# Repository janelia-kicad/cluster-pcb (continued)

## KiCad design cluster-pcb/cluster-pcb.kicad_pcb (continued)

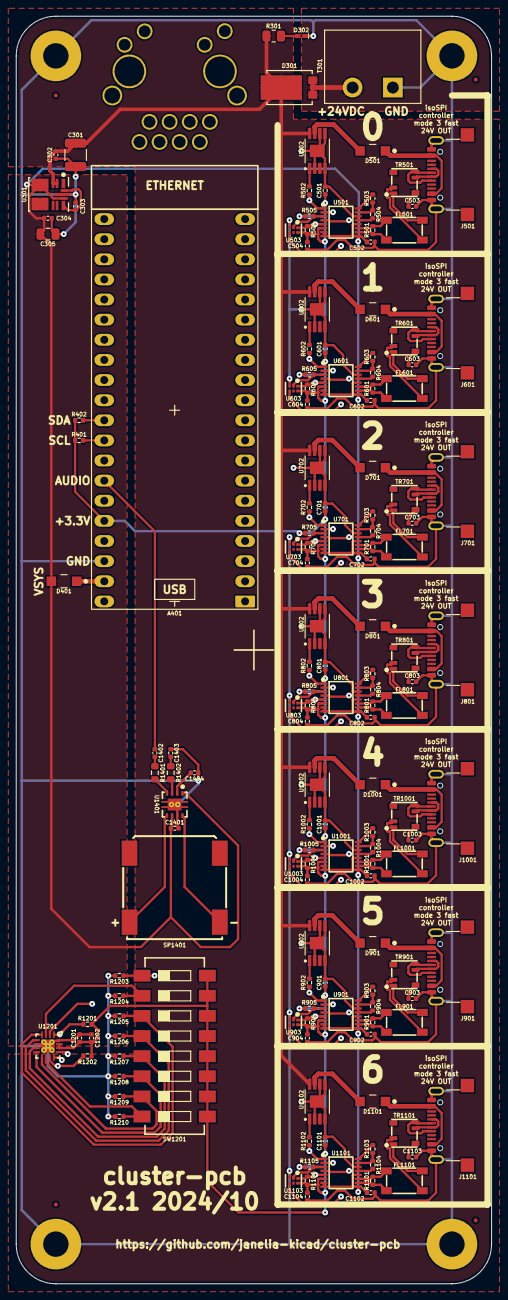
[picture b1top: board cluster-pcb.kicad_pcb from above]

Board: 4 copper layers, 60.0 x 160.0 mm, 163 parts (0 on the bottom side), 130 nets.

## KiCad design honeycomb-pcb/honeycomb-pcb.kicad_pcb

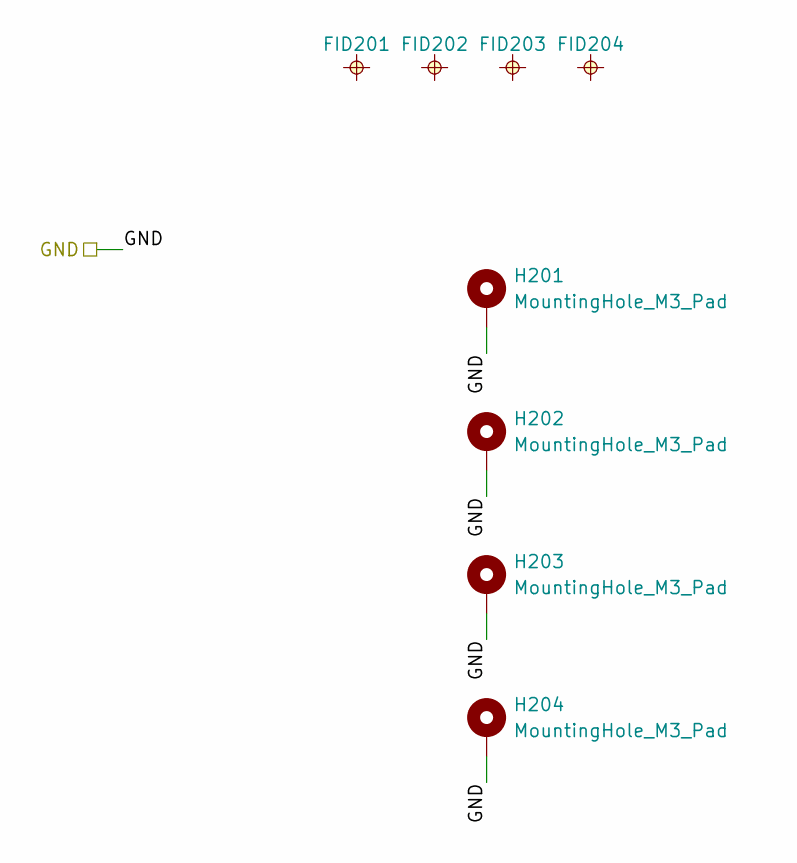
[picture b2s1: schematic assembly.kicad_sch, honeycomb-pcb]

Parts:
FID201, FID202, FID203, FID204: FIDUCIAL_0.5mm_MASK1mm; FIDUCIAL_0.5mm_Mask1mm
H201, H202, H203, H204: MountingHole_M3_Pad; MountingHole_3.2mm_M3_Pad

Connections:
/GND: H201.1, H202.1, H203.1, H204.1; also elsewhere on the board

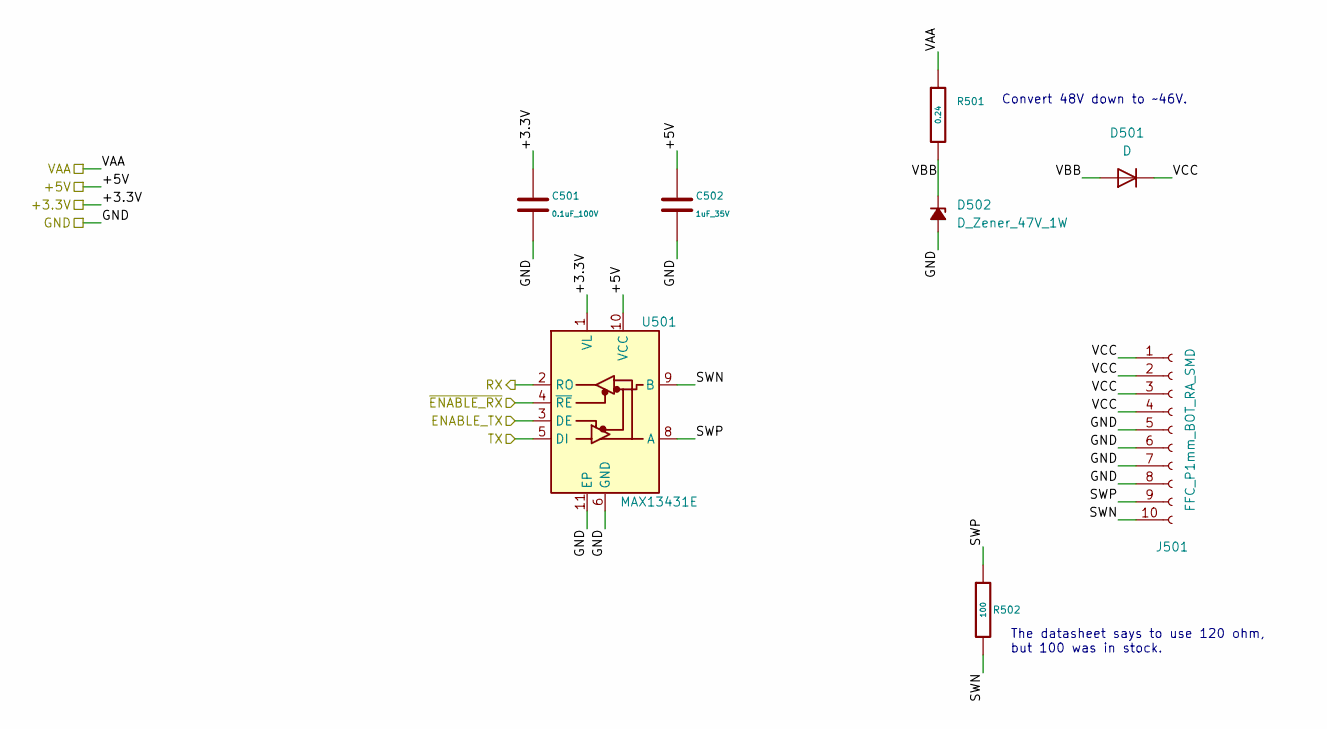
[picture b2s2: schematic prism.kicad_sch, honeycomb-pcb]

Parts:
C501: 0.1uF_100V; C_0402_1005Metric; Manufacturer Part Number GRM155R62A104KE14D; LCSC C162178
C502: 1uF_35V; C_0402_1005Metric; Manufacturer Part Number CL05A105KL5NRNC; LCSC C307413
D501: D; D_SMB; Manufacturer Part Number ES2G; LCSC C4944961
D502: D_Zener_47V_1W; D_SMA; Manufacturer Part Number 1SMAF4756A; LCSC C475448
J501: FFC_P1mm_BOT_RA_SMD; CONN_C2914097; Manufacturer Part Number 1.0K-FX-10PWBG; LCSC C2914097
R501: 0.24; R_2512_6332Metric; Manufacturer Part Number FRL2512JR240TS; LCSC C2960776
R502: 100; R_0402_1005Metric; Manufacturer Part Number 0402WGF1000TCE; LCSC C25076
U501: MAX13431E; 21-0137I_T1033-1_MXM; Manufacturer Part Number MAX13431EETB+T; LCSC C2672811

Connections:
/+3.3V: C501.1, U501.1 (VL); also elsewhere on the board
/+5V: C502.1, U501.10 (VCC); also elsewhere on the board
/ENABLE_TX_0: U501.3 (DE); also elsewhere on the board
/GND: C501.2, C502.2, D502.2 (A), J501.5, J501.6, J501.7, J501.8, U501.6 (GND), U501.11 (EP); also elsewhere on the board
/RX: U501.2 (RO); also elsewhere on the board
/TX: U501.5 (DI); also elsewhere on the board
/VCC: R501.1; also elsewhere on the board
/prism0/SWN: J501.10, R502.2, U501.9 (B)
/prism0/SWP: J501.9, R502.1, U501.8 (A)
/prism0/VBB: D501.2 (A), D502.1 (K), R501.2
/prism0/VCC: D501.1 (K), J501.1, J501.2, J501.3, J501.4
/~ENABLE_RX_0: U501.4 (~RE); also elsewhere on the board

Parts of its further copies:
C601, C701, C801, C901, C1001, C1101: 0.1uF_100V; C_0402_1005Metric; Manufacturer Part Number GRM155R62A104KE14D; LCSC C162178
C602, C702, C802, C902, C1002, C1102: 1uF_35V; C_0402_1005Metric; Manufacturer Part Number CL05A105KL5NRNC; LCSC C307413
D601, D701, D801, D901, D1001, D1101: D; D_SMB; Manufacturer Part Number ES2G; LCSC C4944961
D602, D702, D802, D902, D1002, D1102: D_Zener_47V_1W; D_SMA; Manufacturer Part Number 1SMAF4756A; LCSC C475448
J601, J701, J801, J901, J1001, J1101: FFC_P1mm_BOT_RA_SMD; CONN_C2914097; Manufacturer Part Number 1.0K-FX-10PWBG; LCSC C2914097
R601, R701, R801, R901, R1001, R1101: 0.24; R_2512_6332Metric; Manufacturer Part Number FRL2512JR240TS; LCSC C2960776
R602, R702, R802, R902, R1002, R1102: 100; R_0402_1005Metric; Manufacturer Part Number 0402WGF1000TCE; LCSC C25076
U601, U701, U801, U901, U1001, U1101: MAX13431E; 21-0137I_T1033-1_MXM; Manufacturer Part Number MAX13431EETB+T; LCSC C2672811

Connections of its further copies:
/+3.3V: C601.1, C701.1, C801.1, C901.1, C1001.1, C1101.1, U601.1 (VL), U701.1 (VL), U801.1 (VL), U901.1 (VL), U1001.1 (VL), U1101.1 (VL); also elsewhere on the board
/+5V: C602.1, C702.1, C802.1, C902.1, C1002.1, C1102.1, U601.10 (VCC), U701.10 (VCC), U801.10 (VCC), U901.10 (VCC), U1001.10 (VCC), U1101.10 (VCC); also elsewhere on the board
/ENABLE_TX_1: U601.3 (DE); also elsewhere on the board
/ENABLE_TX_2: U701.3 (DE); also elsewhere on the board
/ENABLE_TX_3: U801.3 (DE); also elsewhere on the board
/ENABLE_TX_4: U1001.3 (DE); also elsewhere on the board
/ENABLE_TX_5: U901.3 (DE); also elsewhere on the board
/ENABLE_TX_6: U1101.3 (DE); also elsewhere on the board
/GND: C601.2, C602.2, C701.2, C702.2, C801.2, C802.2, C901.2, C902.2, C1001.2, C1002.2, C1101.2, C1102.2, D602.2 (A), D702.2 (A), D802.2 (A), D902.2 (A), D1002.2 (A), D1102.2 (A), J601.5, J601.6, J601.7, J601.8, J701.5, J701.6, J701.7, J701.8, J801.5, J801.6, J801.7, J801.8, J901.5, J901.6, J901.7, J901.8, J1001.5, J1001.6, J1001.7, J1001.8, J1101.5, J1101.6, J1101.7, J1101.8, U601.6 (GND), U601.11 (EP), U701.6 (GND), U701.11 (EP), U801.6 (GND), U801.11 (EP), U901.6 (GND), U901.11 (EP), U1001.6 (GND), U1001.11 (EP), U1101.6 (GND), U1101.11 (EP); also elsewhere on the board
/RX: U601.2 (RO), U701.2 (RO), U801.2 (RO), U901.2 (RO), U1001.2 (RO), U1101.2 (RO); also elsewhere on the board
/TX: U601.5 (DI), U701.5 (DI), U801.5 (DI), U901.5 (DI), U1001.5 (DI), U1101.5 (DI); also elsewhere on the board
/VCC: R601.1, R701.1, R801.1, R901.1, R1001.1, R1101.1; also elsewhere on the board
/prism1/SWN: J601.10, R602.2, U601.9 (B)
/prism1/SWP: J601.9, R602.1, U601.8 (A)
/prism1/VBB: D601.2 (A), D602.1 (K), R601.2
/prism1/VCC: D601.1 (K), J601.1, J601.2, J601.3, J601.4
/prism2/SWN: J701.10, R702.2, U701.9 (B)
/prism2/SWP: J701.9, R702.1, U701.8 (A)
/prism2/VBB: D701.2 (A), D702.1 (K), R701.2
/prism2/VCC: D701.1 (K), J701.1, J701.2, J701.3, J701.4
/prism3/SWN: J801.10, R802.2, U801.9 (B)
/prism3/SWP: J801.9, R802.1, U801.8 (A)
/prism3/VBB: D801.2 (A), D802.1 (K), R801.2
/prism3/VCC: D801.1 (K), J801.1, J801.2, J801.3, J801.4
/prism4/SWN: J1001.10, R1002.2, U1001.9 (B)
/prism4/SWP: J1001.9, R1002.1, U1001.8 (A)
/prism4/VBB: D1001.2 (A), D1002.1 (K), R1001.2
/prism4/VCC: D1001.1 (K), J1001.1, J1001.2, J1001.3, J1001.4
/prism5/SWN: J901.10, R902.2, U901.9 (B)
/prism5/SWP: J901.9, R902.1, U901.8 (A)
/prism5/VBB: D901.2 (A), D902.1 (K), R901.2
/prism5/VCC: D901.1 (K), J901.1, J901.2, J901.3, J901.4
/prism6/SWN: J1101.10, R1102.2, U1101.9 (B)
/prism6/SWP: J1101.9, R1102.1, U1101.8 (A)
/prism6/VBB: D1101.2 (A), D1102.1 (K), R1101.2
/prism6/VCC: D1101.1 (K), J1101.1, J1101.2, J1101.3, J1101.4
/~ENABLE_RX_1: U601.4 (~RE); also elsewhere on the board
/~ENABLE_RX_2: U701.4 (~RE); also elsewhere on the board
/~ENABLE_RX_3: U801.4 (~RE); also elsewhere on the board
/~ENABLE_RX_4: U1001.4 (~RE); also elsewhere on the board
/~ENABLE_RX_5: U901.4 (~RE); also elsewhere on the board
/~ENABLE_RX_6: U1101.4 (~RE); also elsewhere on the board

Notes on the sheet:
The datasheet says to use 120 ohm, but 100 was in stock.
Convert 48V down to ~46V.

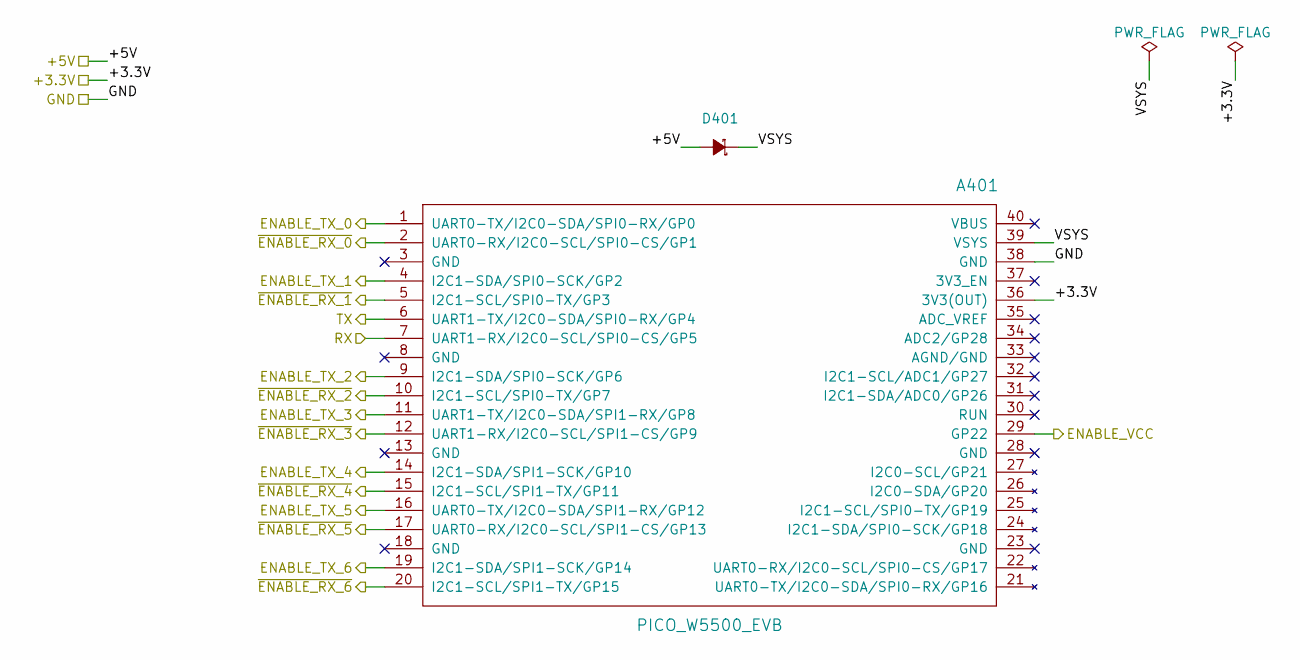
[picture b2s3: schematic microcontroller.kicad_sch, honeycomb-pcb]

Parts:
A401: PICO_W5500_EVB; Pico_Header_Holes
D401: D_SCHOTTKY_20V_1A; DIOM3616X98N; Manufacturer Part Number MBR120VLSFT1G; LCSC C223608

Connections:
/+3.3V: A401.36 (3V3(OUT)); also elsewhere on the board
/+5V: D401.2 (A); also elsewhere on the board
/ENABLE_TX_0: A401.1 (UART0-TX/I2C0-SDA/SPI0-RX/GP0); also elsewhere on the board
/ENABLE_TX_1: A401.4 (I2C1-SDA/SPI0-SCK/GP2); also elsewhere on the board
/ENABLE_TX_2: A401.9 (I2C1-SDA/SPI0-SCK/GP6); also elsewhere on the board
/ENABLE_TX_3: A401.11 (UART1-TX/I2C0-SDA/SPI1-RX/GP8); also elsewhere on the board
/ENABLE_TX_4: A401.14 (I2C1-SDA/SPI1-SCK/GP10); also elsewhere on the board
/ENABLE_TX_5: A401.16 (UART0-TX/I2C0-SDA/SPI1-RX/GP12); also elsewhere on the board
/ENABLE_TX_6: A401.19 (I2C1-SDA/SPI1-SCK/GP14); also elsewhere on the board
/ENABLE_VCC: A401.29 (GP22); also elsewhere on the board
/GND: A401.38 (GND); also elsewhere on the board
/RX: A401.7 (UART1-RX/I2C0-SCL/SPI0-CS/GP5); also elsewhere on the board
/TX: A401.6 (UART1-TX/I2C0-SDA/SPI0-RX/GP4); also elsewhere on the board
/microcontroller/VSYS: A401.39 (VSYS), D401.1 (K)
/~ENABLE_RX_0: A401.2 (UART0-RX/I2C0-SCL/SPI0-CS/GP1); also elsewhere on the board
/~ENABLE_RX_1: A401.5 (I2C1-SCL/SPI0-TX/GP3); also elsewhere on the board
/~ENABLE_RX_2: A401.10 (I2C1-SCL/SPI0-TX/GP7); also elsewhere on the board
/~ENABLE_RX_3: A401.12 (UART1-RX/I2C0-SCL/SPI1-CS/GP9); also elsewhere on the board
/~ENABLE_RX_4: A401.15 (I2C1-SCL/SPI1-TX/GP11); also elsewhere on the board
/~ENABLE_RX_5: A401.17 (UART0-RX/I2C0-SCL/SPI1-CS/GP13); also elsewhere on the board
/~ENABLE_RX_6: A401.20 (I2C1-SCL/SPI1-TX/GP15); also elsewhere on the board

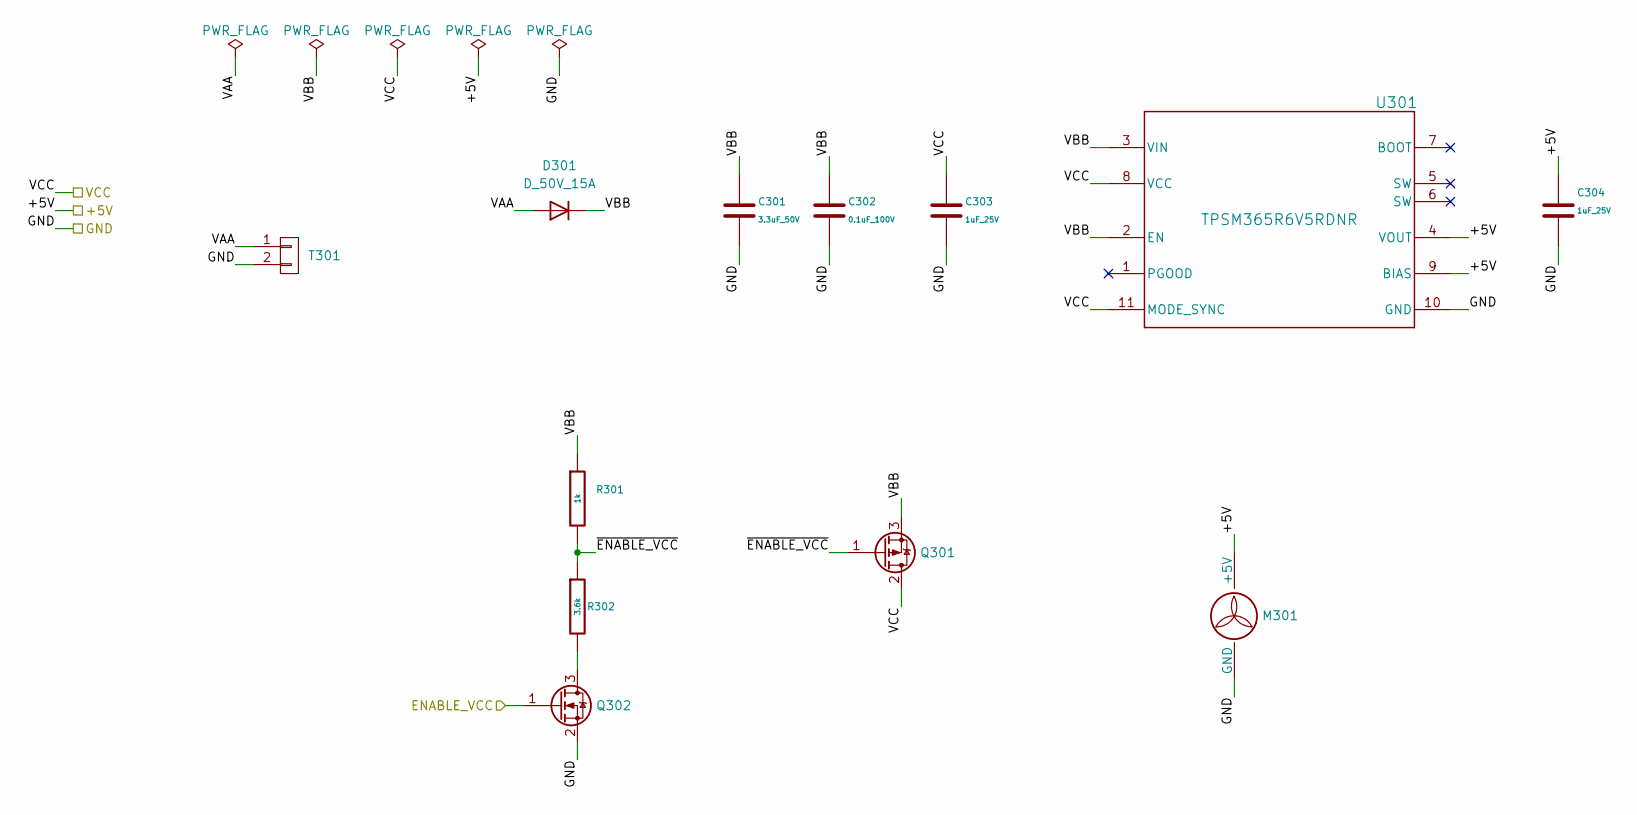
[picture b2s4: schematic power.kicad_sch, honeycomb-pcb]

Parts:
C301: 3.3uF_50V; C_1210_3225Metric; Manufacturer Part Number FS32X335K500EGG; LCSC C1021610
C302: 0.1uF_100V; C_0402_1005Metric; Manufacturer Part Number GRM155R62A104KE14D; LCSC C162178
C303, C304: 1uF_25V; C_0402_1005Metric; Manufacturer Part Number GRT155R61E105KE01D; LCSC C711085
D301: D_50V_15A; POWERDI5_DIO; Manufacturer Part Number SBRT15U50SP5-13; LCSC C211388
M301: Fan_5VDC_25x25x8mm; FAN_5VDC_25x25x8mm; Manufacturer Part Number 255M
Q301: MOSFET-P-CH-EN_60V_50A; TO-252-2; Manufacturer Part Number 30P06-VB; LCSC C709875
Q302: MOSFET-N-CH-EN_100V_260mA; SOT-23; Manufacturer Part Number 2SK1589-T1B-VB; LCSC C724949
R301: 1k; R_0402_1005Metric; Manufacturer Part Number RC0402FR-071KL; LCSC C106235
R302: 3.6k; R_0402_1005Metric; Manufacturer Part Number RM04JTN362; LCSC C162873
T301: TERM_BLK_HDR_2POS_90DEG_0.2IN; PHOENIX_1757242; Manufacturer Part Number 1757242; LCSC C90074
U301: TPSM365R6V5RDNR; RDN0011A-MFG; Manufacturer Part Number TPSM365R6V5RDNR; LCSC C19078014

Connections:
/+5V: C304.1, M301.1 (+5V), U301.4 (VOUT), U301.9 (BIAS); also elsewhere on the board
/ENABLE_VCC: Q302.1 (G); also elsewhere on the board
/GND: C301.2, C302.2, C303.2, C304.2, M301.2 (GND), M301.3 (MH), Q302.2 (S), T301.2, U301.10 (GND); also elsewhere on the board
/VCC: C303.1, Q301.2 (D), U301.8 (VCC), U301.11 (MODE_SYNC); also elsewhere on the board
/power/VAA: D301.2 (A), T301.1
/power/VBB: C301.1, C302.1, D301.1 (K), Q301.3 (S), R301.1, U301.2 (EN), U301.3 (VIN)
/power/~ENABLE_VCC: Q301.1 (G), R301.2, R302.1
unnamed: Q302.3 (D), R302.2

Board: 4 copper layers, 78 parts (6 on the bottom side), 54 nets, no tracks yet.

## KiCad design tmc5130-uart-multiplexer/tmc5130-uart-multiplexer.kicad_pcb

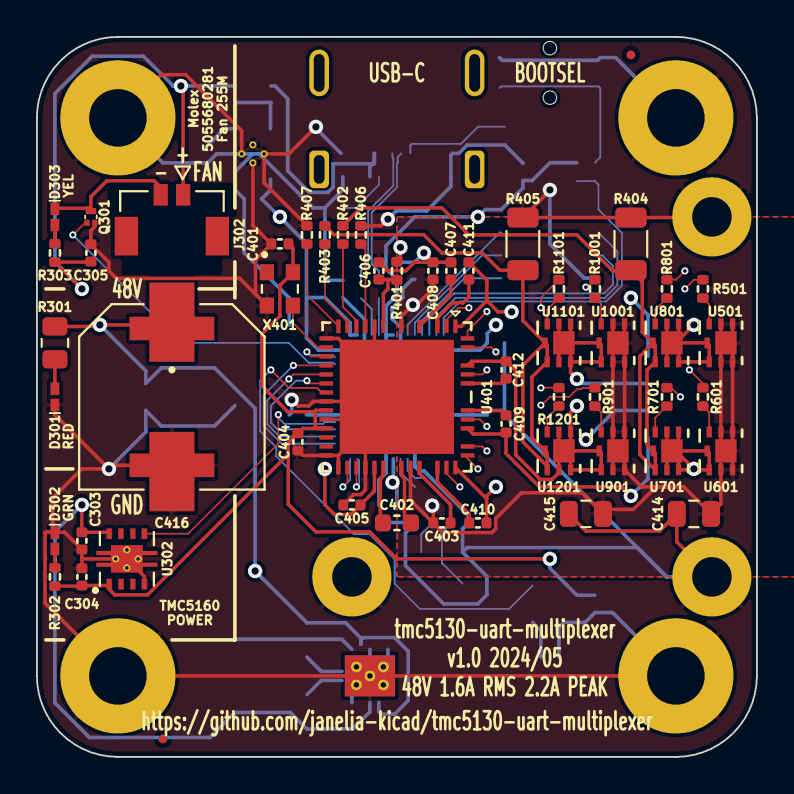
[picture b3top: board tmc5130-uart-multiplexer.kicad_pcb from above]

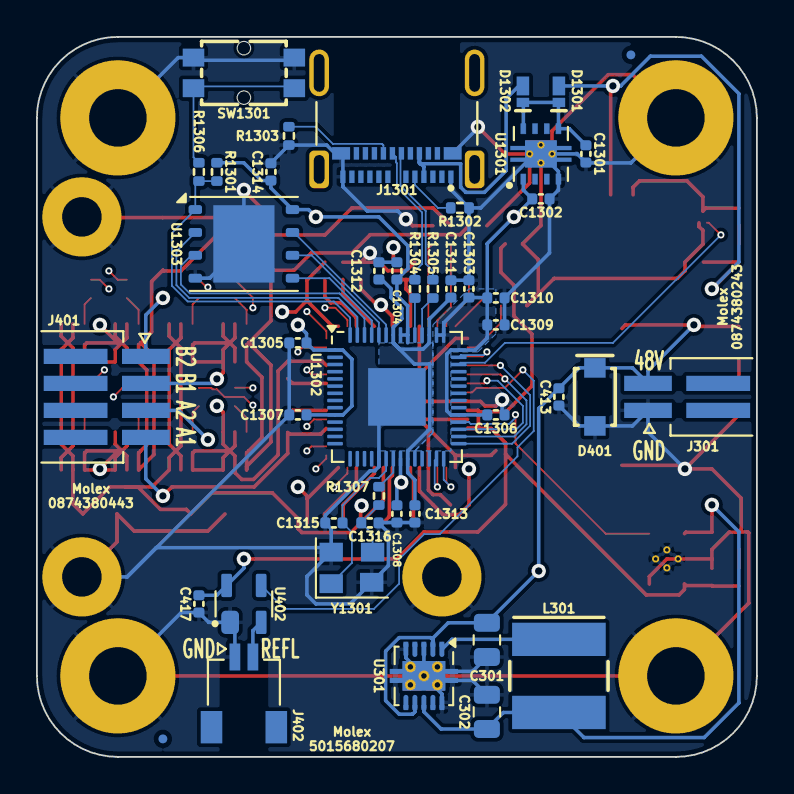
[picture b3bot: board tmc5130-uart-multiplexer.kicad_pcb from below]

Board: 4 copper layers, 40.0 x 40.0 mm, 103 parts (44 on the bottom side), 76 nets.

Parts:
C301, C414, C415: 2.2uF_100V; C_0805_2012Metric
C302: 47uF_10V; C_0805_2012Metric
C303, C304, C305, C1301, C1302: 1uF_25V; C_0402_1005Metric
C401, C403, C404, C408, C413, C417, C1304, C1305, C1306, C1307, C1308, C1309, C1310, C1312, C1313, C1314: 0.1uF_100V; C_0402_1005Metric
C402: 22nF_100V; C_0603_1608Metric
C405: 0.47uF_35V; C_0402_1005Metric
C406, C407: 2.2uF_35V; C_0402_1005Metric
C409, C410, C411, C412: 0.22uF_25V; C_0402_1005Metric
C416: 220uF_63V; CP_Hybrid_EEHZS1H221V
C1303, C1311: 1uF_35V; C_0402_1005Metric
C1315, C1316: 15pF_25V; C_0402_1005Metric
D301: LED_RED; LED_0402-1005_KNB
D302: LED_GRN; LED_0402-1005_KNB
D303: LED_YEL; LED_0402-1005_KNB
D401: D_Zener_48V_2.6A; SMFSeries_LTF
D1301, D1302: D_SCHOTTKY_40V_2A; CR_DSN2_152AB-C_OSI
FID201, FID202, FID203, FID204: FIDUCIAL_0.5mm_MASK1mm; FIDUCIAL_0.5mm_Mask1mm
H201, H202, H203, H204: MountingHole_M3_Pad; MountingHole_3.2mm_M3_Pad
J301: Molex_Pico-SPOX_Horizontal; Molex_Pico-SPOX-87438_1x02-P1.5mm_Horizontal
J302: Molex_Pico-Lock-PLUS_Vertical; Molex_Micro-Lock-PLUS-505568_1x02_P1.25mm_Vertical
J401: Molex_Pico-SPOX_Horizontal; Molex_Pico-SPOX-87438_1x04-P1.5mm_Horizontal
J402: Molex_Pico-Clasp_Horizontal; Molex_Pico-Clasp-501568_1x02_P1mm_Horizontal
J1301: Connector_USB_C_Receptacle; USB_C_Receptacle_Amphenol_10152803-00011LF
L301: 150uH_553mA; IND_CB_SD25
M301: Fan_5VDC_25x25x8mm; FAN_5VDC_25x25x8mm
Q301: MOSFET-N-CH; XFDFN-3
R301: 2.32k; R_0805_2012Metric
R302: 64.9; R_0402_1005Metric
R303: 249; R_0402_1005Metric
R401: 2.2; R_0402_1005Metric
R402, R403, R406, R407: 47; R_0402_1005Metric
R404, R405: 0.15; R_1206_3216Metric
R501, R601, R701, R801, R901, R1001, R1101, R1201: 15; R_0402_1005Metric
R1301: 10.0k; R_0402_1005Metric
R1302, R1303: 5.1k; R_0402_1005Metric
R1304, R1305: 27; R_0402_1005Metric
R1306, R1307: 1k; R_0402_1005Metric
SW1301: Switch_Tactile_SPST-NO_SMT_Side; SMT_1045822_WRE
U301: Switching_5V_500mA; Texas_S-PVSON-N10_ThermalVias
U302, U1301: Linear_3.3V_1A; TPS737Q1
U401: TMC5160A-WA; 21-100593_ADI
U402: MAX6816; SOT192P237X122-4N
U501, U601, U701, U801, U901, U1001, U1101, U1201: BUK7D36-60EX; BUK7D3660EX_NEX
U1302: MCU_RP2040; QFN-56-1EP_7x7mm_P0.4mm_EP3.2x3.2mm
U1303: Memory_Flash_W25Q128JVZPIQ; WSON-8-1EP_6x5mm_P1.27mm_EP3.4x4.3mm
X401: 16MHz; OSC_ECS-2520S33-160-FN-TR
Y1301: Crystal_12MHz; Crystal_SMD_Abracon_ABM8-4Pin_3.2x2.5mm

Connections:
/+5V: C302.1, C303.1, C305.1, D1301.2 (A), J302.1, L301.2, R303.1, U301.8 (VOUT), U302.8 (IN)
/DIAG0: U401.27 (SWN/DIAG0), U1302.28 (GPIO17)
/DIAG1: U401.28 (SWP/DIAG1), U1302.27 (GPIO16)
/ENABLE_FAN: Q301.1 (G), U1302.40 (GPIO28_ADC2)
/ENABLE_VIO: U302.5 (EN), U1302.32 (GPIO21)
/GND: C301.2, C302.2, C303.2, C304.2, C305.2, C401.2, C404.2, C405.2, C406.2, C407.2, C408.2, C413.2, C414.2, C415.2, C416.2, C417.2, C1301.2, C1302.2, C1303.2, C1304.2, C1305.2, C1306.2, C1307.2, C1308.2, C1309.2, C1310.2, C1311.2, C1312.2, C1313.2, C1314.2, C1315.2, C1316.2, D301.1 (K), D302.1 (K), D401.2 (A), H201.1, H202.1, H203.1, H204.1, J301.1, J402.1, J1301.A1 (GND), J1301.A12 (GND), J1301.B1 (GND), J1301.B12 (GND), M301.1, M301.2, M301.3, Q301.2 (S), R404.2, R405.2, R406.2, R407.2, R1302.2, R1303.2, SW1301.2, SW1301.4, U301.3 (ILIM), U301.5 (RT), U301.10 (GND), U301.11 (GND), U302.4 (GND), U302.9 (PAD), U401.7 (GNDA), U401.12 (TST_MODE), U401.19 (REFR/DIR), U401.21 (SD_MODE), U401.25 (GNDD), U401.26 (ENCN/DCO/CFG6), U401.29 (~DRV_EN), U401.48 (EP), U402.1 (GND), U1301.4 (GND), U1301.9 (PAD), U1302.19 (TESTEN), U1302.57 (GND), U1303.4 (GND), U1303.9 (EP), X401.2 (GND), Y1301.2, Y1301.4
/MISO: U401.17 (SDO/CFG0), U1302.31 (GPIO20)
/MOSI: U401.16 (SDI/CFG1), U1302.30 (GPIO19)
/SCK: U401.15 (SCK/CFG2), U1302.29 (GPIO18)
/VIO: C304.1, C401.1, C404.1, C417.1, R302.1, U302.1 (OUT), U401.20 (VCC_IO), U401.22 (SPI_MODE), U402.4 (Vcc), X401.4 (VDD)
/VM: C301.1, C403.1, C408.1, C413.1, C414.1, C415.1, C416.1, D401.1 (K), J301.2, R301.1, U301.2 (VIN), U301.7 (EN), U401.5 (VSA), U401.33 (VS), U501.1 (D), U501.2 (D), U501.5 (D), U501.6 (D), U501.7 (D), U601.1 (D), U601.2 (D), U601.5 (D), U601.6 (D), U601.7 (D), U901.1 (D), U901.2 (D), U901.5 (D), U901.6 (D), U901.7 (D), U1001.1 (D), U1001.2 (D), U1001.5 (D), U1001.6 (D), U1001.7 (D)
/power/FAN-: D303.1 (K), J302.2, Q301.3 (D)
/power/LED_GRN+: D302.2 (A), R302.2
/power/LED_RED+: D301.2 (A), R301.2
/power/LED_YEL+: D303.2 (A), R303.2
/power/SW: L301.1, U301.1 (SW)
/rp2040/+1.1V: C1311.1, C1312.1, C1313.1, U1302.23 (DVDD), U1302.45 (VREG_VOUT), U1302.50 (DVDD)
/rp2040/+3.3V: C1302.1, C1303.1, C1304.1, C1305.1, C1306.1, C1307.1, C1308.1, C1309.1, C1310.1, C1314.1, R1301.2, U1301.1 (OUT), U1302.1 (IOVDD), U1302.10 (IOVDD), U1302.22 (IOVDD), U1302.33 (IOVDD), U1302.42 (IOVDD), U1302.43 (ADC_AVDD), U1302.44 (VREG_IN), U1302.48 (USB_VDD), U1302.49 (IOVDD), U1303.8 (VCC)
/rp2040/CC1: J1301.A5 (CC1), R1302.1
/rp2040/CC2: J1301.B5 (CC2), R1303.1
/rp2040/D+: J1301.B6 (D+), R1304.1
/rp2040/D-: J1301.B7 (D-), R1305.1
/rp2040/QSPI_SCLK: U1302.52 (QSPI_SCLK), U1303.6 (CLK)
/rp2040/QSPI_SD0: U1302.53 (QSPI_SD0), U1303.5 (DI(IO0))
/rp2040/QSPI_SD1: U1302.55 (QSPI_SD1), U1303.2 (DO(IO1))
/rp2040/QSPI_SD2: U1302.54 (QSPI_SD2), U1303.3 (IO2)
/rp2040/QSPI_SD3: U1302.51 (QSPI_SD3), U1303.7 (IO3)
/rp2040/QSPI_SS: R1301.1, R1306.1, U1302.56 (QSPI_SS), U1303.1 (~CS)
/rp2040/USB_N: R1305.2, U1302.46 (USB_DM)
/rp2040/USB_P: R1304.2, U1302.47 (USB_DP)
/rp2040/VBUS: D1302.2 (A), J1301.A4 (VBUS), J1301.B9 (VBUS)
/rp2040/VSYS: C1301.1, D1301.1 (K), D1302.1 (K), U1301.5 (EN), U1301.8 (IN)
/rp2040/XIN: C1315.1, U1302.20 (XIN), Y1301.1
/rp2040/XOUT: R1307.1, U1302.21 (XOUT)
/rp2040/XOUTB: C1316.1, R1307.2, Y1301.3
/rp2040/~USB_BOOT: R1306.2, SW1301.1, SW1301.3
/tmc5160/5VOUT: C406.1, R401.2, U401.6 (5VOUT)
/tmc5160/12VOUT: C407.1, U401.4 (12VOUT)
/tmc5160/BMA1: C409.2, J401.4, U401.40 (BMA1), U501.4 (S), U501.8 (S), U801.1 (D), U801.2 (D), U801.5 (D), U801.6 (D), U801.7 (D)
/tmc5160/BMA2: C410.2, J401.3, U401.37 (BMA2), U601.4 (S), U601.8 (S), U701.1 (D), U701.2 (D), U701.5 (D), U701.6 (D), U701.7 (D)
/tmc5160/BMB1: C411.2, J401.2, U401.1 (BMB1), U1001.4 (S), U1001.8 (S), U1101.1 (D), U1101.2 (D), U1101.5 (D), U1101.6 (D), U1101.7 (D)
/tmc5160/BMB2: C412.2, J401.1, U401.45 (BMB2), U901.4 (S), U901.8 (S), U1201.1 (D), U1201.2 (D), U1201.5 (D), U1201.6 (D), U1201.7 (D)
/tmc5160/CA1: C409.1, U401.42 (CA1)
/tmc5160/CA2: C410.1, U401.35 (CA2)
/tmc5160/CB1: C411.1, U401.3 (CB1)
/tmc5160/CB2: C412.1, U401.43 (CB2)
/tmc5160/CLOCK: U401.13 (CLK), X401.3 (OUT)
/tmc5160/CPI: C402.2, U401.32 (CPI)
/tmc5160/CPO: C402.1, U401.31 (CPO)
/tmc5160/HA1: R501.1, U401.41 (HA1)
/tmc5160/HA2: R601.1, U401.36 (HA2)
/tmc5160/HB1: R1001.1, U401.2 (HB1)
/tmc5160/HB2: R901.1, U401.44 (HB2)
/tmc5160/LA1: R801.1, U401.39 (LA1)
/tmc5160/LA2: R701.1, U401.38 (LA2)
/tmc5160/LB1: R1101.1, U401.47 (LB1)
/tmc5160/LB2: R1201.1, U401.46 (LB2)
/tmc5160/REFL: J402.2, U402.2 (IN)
/tmc5160/REFL_DEBOUNCED: U401.18 (REFL/STEP), U402.3 (OUT)
/tmc5160/SRA: R402.2, R404.1, U701.4 (S), U701.8 (S), U801.4 (S), U801.8 (S)
/tmc5160/SRAH: R402.1, U401.9 (SRAH)
/tmc5160/SRAL: R406.1, U401.8 (SRAL)
/tmc5160/SRB: R403.2, R405.1, U1101.4 (S), U1101.8 (S), U1201.4 (S), U1201.8 (S)
/tmc5160/SRBH: R403.1, U401.10 (SRBH)
/tmc5160/SRBL: R407.1, U401.11 (SRBL)
/tmc5160/VCC: C405.1, R401.1, U401.30 (VCC)
/tmc5160/VCP: C403.2, U401.34 (VCP)
/tmc5160/mosfet1/GATEB: R501.2, U501.3 (G)
/tmc5160/mosfet2/GATEB: R601.2, U601.3 (G)
/tmc5160/mosfet3/GATEB: R801.2, U801.3 (G)
/tmc5160/mosfet4/GATEB: R701.2, U701.3 (G)
/tmc5160/mosfet5/GATEB: R1001.2, U1001.3 (G)
/tmc5160/mosfet6/GATEB: R901.2, U901.3 (G)
/tmc5160/mosfet7/GATEB: R1101.2, U1101.3 (G)
/tmc5160/mosfet8/GATEB: R1201.2, U1201.3 (G)
/~CS: U401.14 (~CS/CFG3), U1302.41 (GPIO29_ADC3)

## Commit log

2024-06-28 Deleted unused schematics
2024-07-02 Update components
2024-07-09 Add components
2024-07-10 Change sheets
2024-07-11 tmc51x0-multiplexer-uart -> tmc5130-uart-multiplexer
2024-07-11 Fix some design rule checks
2024-07-12 tmc5130-uart-multiplexer -> honeycomb-pcb
2024-07-12 Update metadata
2024-07-12 motor -> prism
2024-07-16 Update BOM
2024-07-16 Last update before renaming
2024-07-16 honeycomb-pcb -> cluster-pcb
2024-07-16 Initial layout
2024-07-18 Add tracks
2024-07-25 Add some more traces
2024-07-26 Finalize layout
2024-07-26 Save again
2024-08-20 First steps towards v1.1
2024-08-26 Update documentation
2024-08-30 Add documentation
2024-08-30 Add address
2024-09-03 Add i2c pullups
2024-09-10 100 -> 120 ohm and change connectors
2024-09-10 Adjust schematic
2024-09-12 Update schematic
2024-09-13 Fix ERC issues
2024-09-13 Rearrange footprints
2024-09-13 Routed most tracks
2024-09-16 Update supplemental bom
2024-09-20 First SPI changes
2024-09-27 Progress toward v2.0
2024-09-27 Initial pcb layout
2024-09-27 Adjust solder pads
2024-09-30 Progress towards layout
2024-09-30 Update routing
2024-10-01 Finish routing
2024-10-01 Finish v2.0
2024-10-21 Adjust silkscreen
2024-10-21 Finish v1.3
2024-10-21 Progress toward schematic v2.1
2024-10-22 Finished v2.1
2025-05-23 Update kicad to version 9
